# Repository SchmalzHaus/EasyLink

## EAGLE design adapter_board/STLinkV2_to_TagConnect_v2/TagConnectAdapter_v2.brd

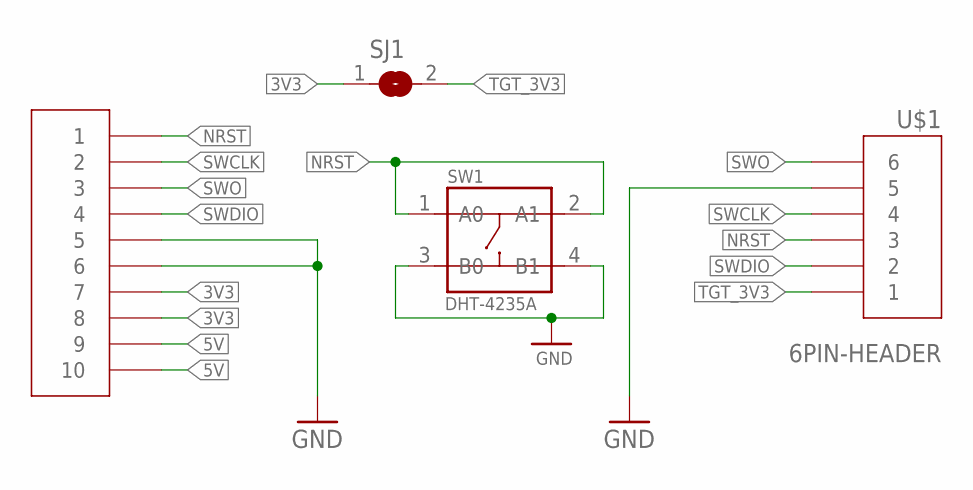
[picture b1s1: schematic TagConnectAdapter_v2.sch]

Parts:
SJ1: SJ
SW1: DHT-4235A; SW4-SMD-4.2X3.2X2.5MM
U$1: 6PIN-HEADER; 2X3_BOARD_EDGE
U$2: SFH11-2X5STRAIGHT; SFH11-2X5-STRAIGHT

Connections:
3V3: SJ1.1, U$2.P7 (7), U$2.P8 (8)
5V: U$2.P9 (9), U$2.P10 (10)
GND: SW1.3 (B0), SW1.4 (B1), U$1.P5 (5), U$2.P5 (5), U$2.P6 (6)
NRST: SW1.1 (A0), SW1.2 (A1), U$1.P3 (3), U$2.P1 (1)
SWCLK: U$1.P4 (4), U$2.P2 (2)
SWDIO: U$1.P2 (2), U$2.P4 (4)
SWO: U$1.P6 (6), U$2.P3 (3)
TGT_3V3: SJ1.2, U$1.P1 (1)

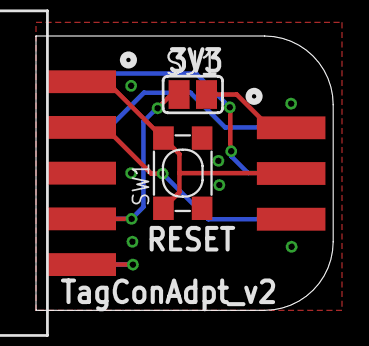
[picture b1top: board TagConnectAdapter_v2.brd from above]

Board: 2 copper layers, 16.5 x 15.2 mm, 4 parts (0 on the bottom side), 8 nets.

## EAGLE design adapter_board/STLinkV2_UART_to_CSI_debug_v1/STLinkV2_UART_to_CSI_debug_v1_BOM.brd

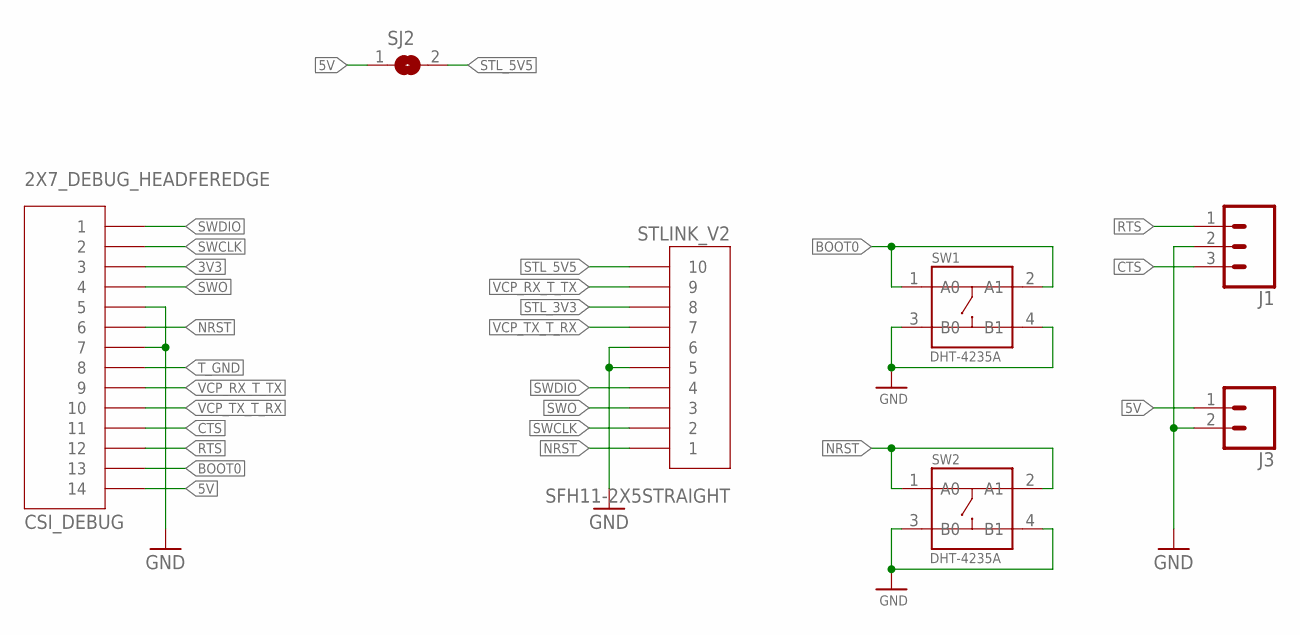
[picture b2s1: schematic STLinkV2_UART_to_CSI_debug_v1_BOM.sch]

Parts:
CSI_DEBUG: 2X7_DEBUG_HEADFEREDGE; 2X7_MALE_BOARD_STRADDLE
J1: CONN_03; 1X03
J3: CONN_02; 1X02
SJ2: SJ
STLINK_V2: SFH11-2X5STRAIGHT; SFH11-2X5-STRAIGHT
SW1, SW2: DHT-4235A; SW4-SMD-4.2X3.2X2.5MM

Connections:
3V3: CSI_DEBUG.P$3 (3)
5V: CSI_DEBUG.P$14 (14), J3.1, SJ2.1
BOOT0: CSI_DEBUG.P$13 (13), SW1.1 (A0), SW1.2 (A1)
CTS: CSI_DEBUG.P$11 (11), J1.3
GND: CSI_DEBUG.P$5 (5), CSI_DEBUG.P$7 (7), J1.2, J3.2, STLINK_V2.P5 (5), STLINK_V2.P6 (6), SW1.3 (B0), SW1.4 (B1), SW2.3 (B0), SW2.4 (B1)
NRST: CSI_DEBUG.P$6 (6), STLINK_V2.P1 (1), SW2.1 (A0), SW2.2 (A1)
RTS: CSI_DEBUG.P$12 (12), J1.1
STL_3V3: STLINK_V2.P8 (8)
STL_5V5: SJ2.2, STLINK_V2.P10 (10)
SWCLK: CSI_DEBUG.P$2 (2), STLINK_V2.P2 (2)
SWDIO: CSI_DEBUG.P$1 (1), STLINK_V2.P4 (4)
SWO: CSI_DEBUG.P$4 (4), STLINK_V2.P3 (3)
T_GND: CSI_DEBUG.P$8 (8)
VCP_RX_T_TX: CSI_DEBUG.P$9 (9), STLINK_V2.P9 (9)
VCP_TX_T_RX: CSI_DEBUG.P$10 (10), STLINK_V2.P7 (7)

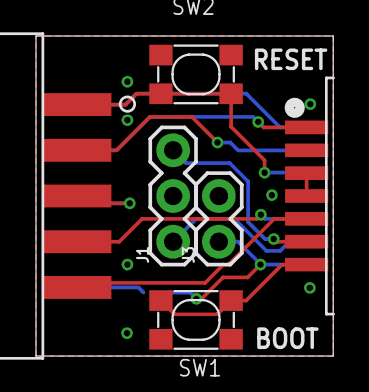
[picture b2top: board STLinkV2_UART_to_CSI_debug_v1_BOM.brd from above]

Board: 2 copper layers, 16.5 x 17.8 mm, 7 parts (1 on the bottom side), 12 nets.

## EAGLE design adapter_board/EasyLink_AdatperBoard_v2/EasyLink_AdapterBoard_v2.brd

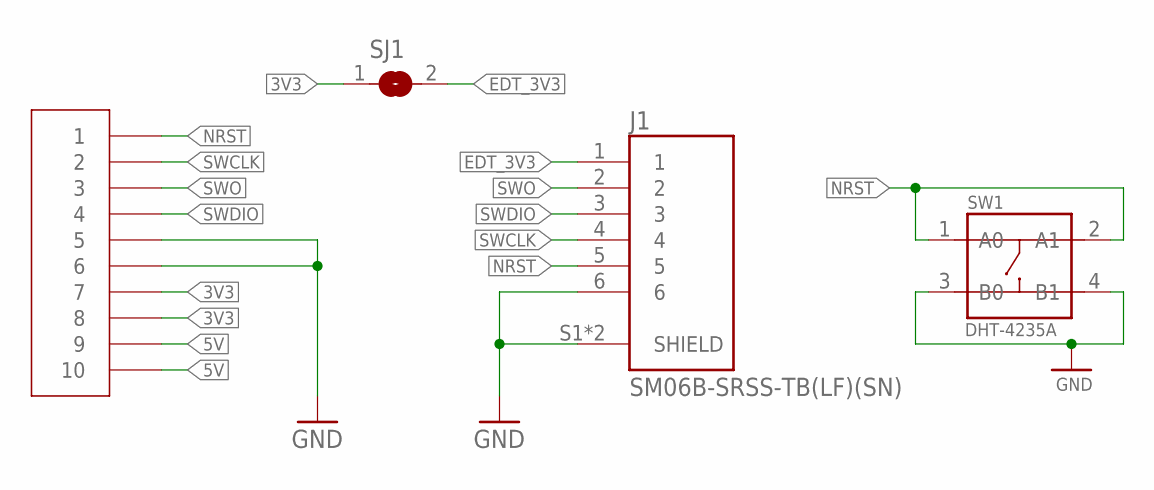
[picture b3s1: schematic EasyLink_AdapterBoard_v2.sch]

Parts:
J1: SM06B-SRSS-TB(LF)(SN); JST_SM06B-SRSS-TB(LF)(SN)
SJ1: SJ
SW1: DHT-4235A; SW4-SMD-4.2X3.2X2.5MM
U$2: SFH11-2X5STRAIGHT; SFH11-2X5-STRAIGHT

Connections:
3V3: SJ1.1, U$2.P7 (7), U$2.P8 (8)
5V: U$2.P9 (9), U$2.P10 (10)
EDT_3V3: J1.1, SJ1.2
GND: J1.6, J1.S1 (SHIELD), J1.S2 (SHIELD), SW1.3 (B0), SW1.4 (B1), U$2.P5 (5), U$2.P6 (6)
NRST: J1.5, SW1.1 (A0), SW1.2 (A1), U$2.P1 (1)
SWCLK: J1.4, U$2.P2 (2)
SWDIO: J1.3, U$2.P4 (4)
SWO: J1.2, U$2.P3 (3)

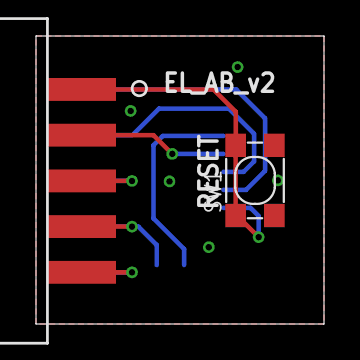
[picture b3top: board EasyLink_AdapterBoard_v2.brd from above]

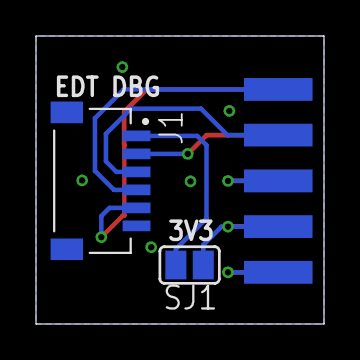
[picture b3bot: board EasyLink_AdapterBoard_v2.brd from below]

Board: 2 copper layers, 16.0 x 16.0 mm, 4 parts (2 on the bottom side), 8 nets.

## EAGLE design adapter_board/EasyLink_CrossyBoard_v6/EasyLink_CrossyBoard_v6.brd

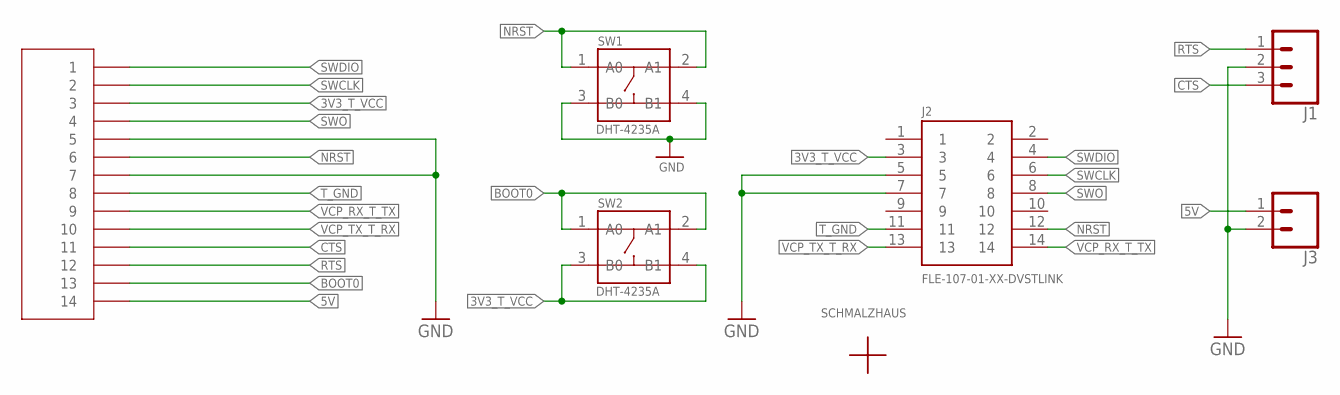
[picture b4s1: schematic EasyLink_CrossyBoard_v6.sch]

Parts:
CN2: 2X7_DEBUG_HEADFEREDGE; 2X7_MALE_BOARD_STRADDLE
J1: CONN_03; 1X03
J2: FLE-107-01-XX-DVSTLINK; ST_LINK_V3_DIRECT
J3: CONN_02; 1X02
SW1, SW2: DHT-4235A; SW4-SMD-4.2X3.2X2.5MM
U$2: SCHMALZHAUSSCHMALZHAUS_SMALL; SCHMALZHAUS_SMALL

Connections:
3V3_T_VCC: CN2.P$3 (3), J2.3, SW2.3 (B0), SW2.4 (B1)
5V: CN2.P$14 (14), J3.1
BOOT0: CN2.P$13 (13), SW2.1 (A0), SW2.2 (A1)
CTS: CN2.P$11 (11), J1.3
GND: CN2.P$5 (5), CN2.P$7 (7), J1.2, J2.5, J2.7, J3.2, SW1.3 (B0), SW1.4 (B1)
NRST: CN2.P$6 (6), J2.12, SW1.1 (A0), SW1.2 (A1)
RTS: CN2.P$12 (12), J1.1
SWCLK: CN2.P$2 (2), J2.6
SWDIO: CN2.P$1 (1), J2.4
SWO: CN2.P$4 (4), J2.8
T_GND: CN2.P$8 (8), J2.11
VCP_RX_T_TX: CN2.P$9 (9), J2.14
VCP_TX_T_RX: CN2.P$10 (10), J2.13

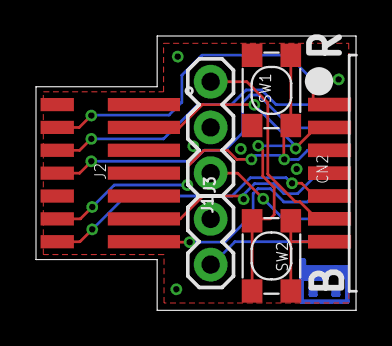
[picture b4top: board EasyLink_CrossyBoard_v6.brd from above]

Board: 2 copper layers, 17.8 x 15.2 mm, 7 parts (1 on the bottom side), 13 nets.

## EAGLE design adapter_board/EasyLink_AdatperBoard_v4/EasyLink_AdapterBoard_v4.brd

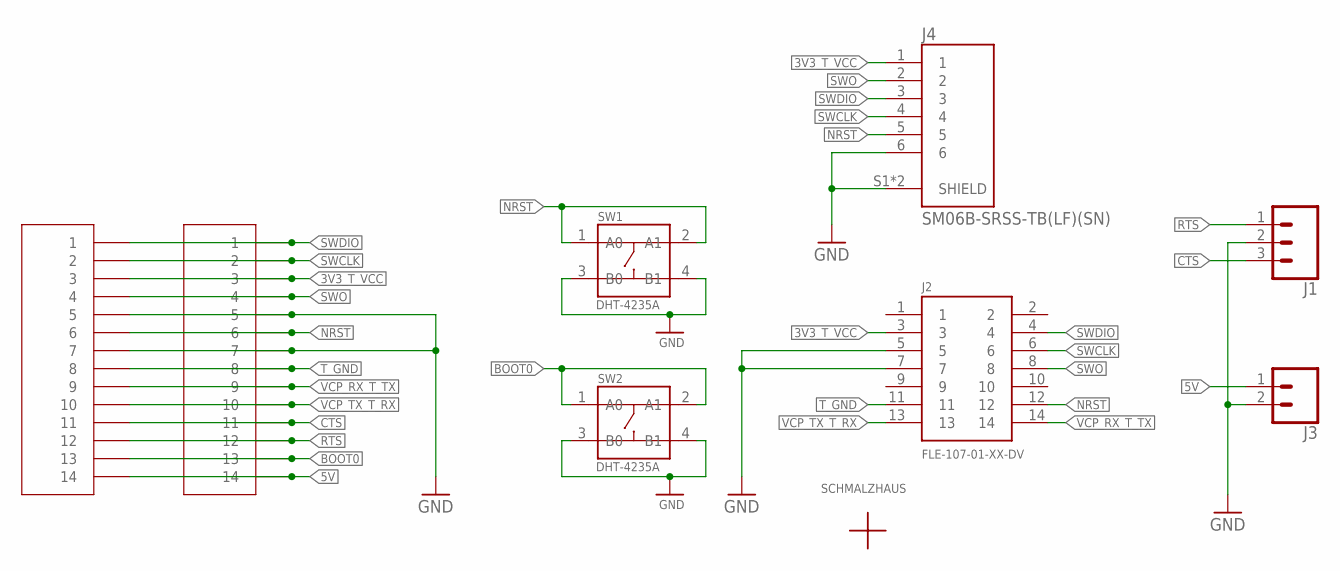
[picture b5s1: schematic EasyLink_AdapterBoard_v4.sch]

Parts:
CN1: 2X7_DEBUG_HEADFER; 20021121_2X7_SMT_MALE
CN2: 2X7_DEBUG_HEADFEREDGE; 2X7_MALE_BOARD_STRADDLE
J1: CONN_03; 1X03
J2: FLE-107-01-XX-DV
J3: CONN_02; 1X02
J4: SM06B-SRSS-TB(LF)(SN); JST_SM06B-SRSS-TB(LF)(SN)
SW1, SW2: DHT-4235A; SW4-SMD-4.2X3.2X2.5MM
U$2: SCHMALZHAUSSCHMALZHAUS_SMALL; SCHMALZHAUS_SMALL

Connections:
3V3_T_VCC: CN1.P$3 (3), CN2.P$3 (3), J2.3, J4.1
5V: CN1.P$14 (14), CN2.P$14 (14), J3.1
BOOT0: CN1.P$13 (13), CN2.P$13 (13), SW2.1 (A0), SW2.2 (A1)
CTS: CN1.P$11 (11), CN2.P$11 (11), J1.3
GND: CN1.P$5 (5), CN1.P$7 (7), CN2.P$5 (5), CN2.P$7 (7), J1.2, J2.5, J2.7, J3.2, J4.6, J4.S1 (SHIELD), J4.S2 (SHIELD), SW1.3 (B0), SW1.4 (B1), SW2.3 (B0), SW2.4 (B1)
NRST: CN1.P$6 (6), CN2.P$6 (6), J2.12, J4.5, SW1.1 (A0), SW1.2 (A1)
RTS: CN1.P$12 (12), CN2.P$12 (12), J1.1
SWCLK: CN1.P$2 (2), CN2.P$2 (2), J2.6, J4.4
SWDIO: CN1.P$1 (1), CN2.P$1 (1), J2.4, J4.3
SWO: CN1.P$4 (4), CN2.P$4 (4), J2.8, J4.2
T_GND: CN1.P$8 (8), CN2.P$8 (8), J2.11
VCP_RX_T_TX: CN1.P$9 (9), CN2.P$9 (9), J2.14
VCP_TX_T_RX: CN1.P$10 (10), CN2.P$10 (10), J2.13

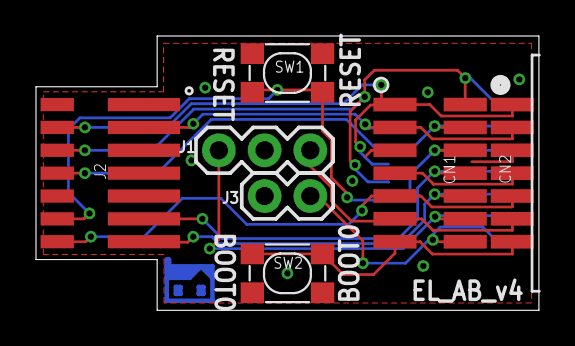
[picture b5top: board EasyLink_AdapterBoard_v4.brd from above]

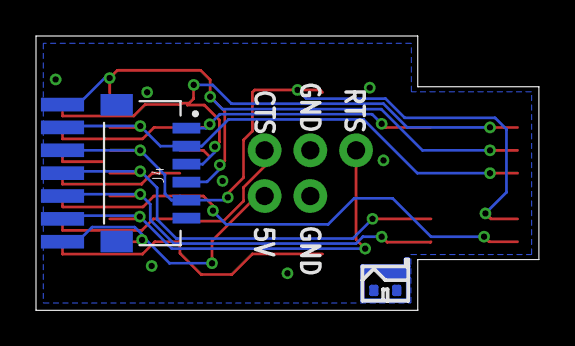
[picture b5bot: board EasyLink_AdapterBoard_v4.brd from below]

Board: 2 copper layers, 27.9 x 15.2 mm, 9 parts (2 on the bottom side), 13 nets.

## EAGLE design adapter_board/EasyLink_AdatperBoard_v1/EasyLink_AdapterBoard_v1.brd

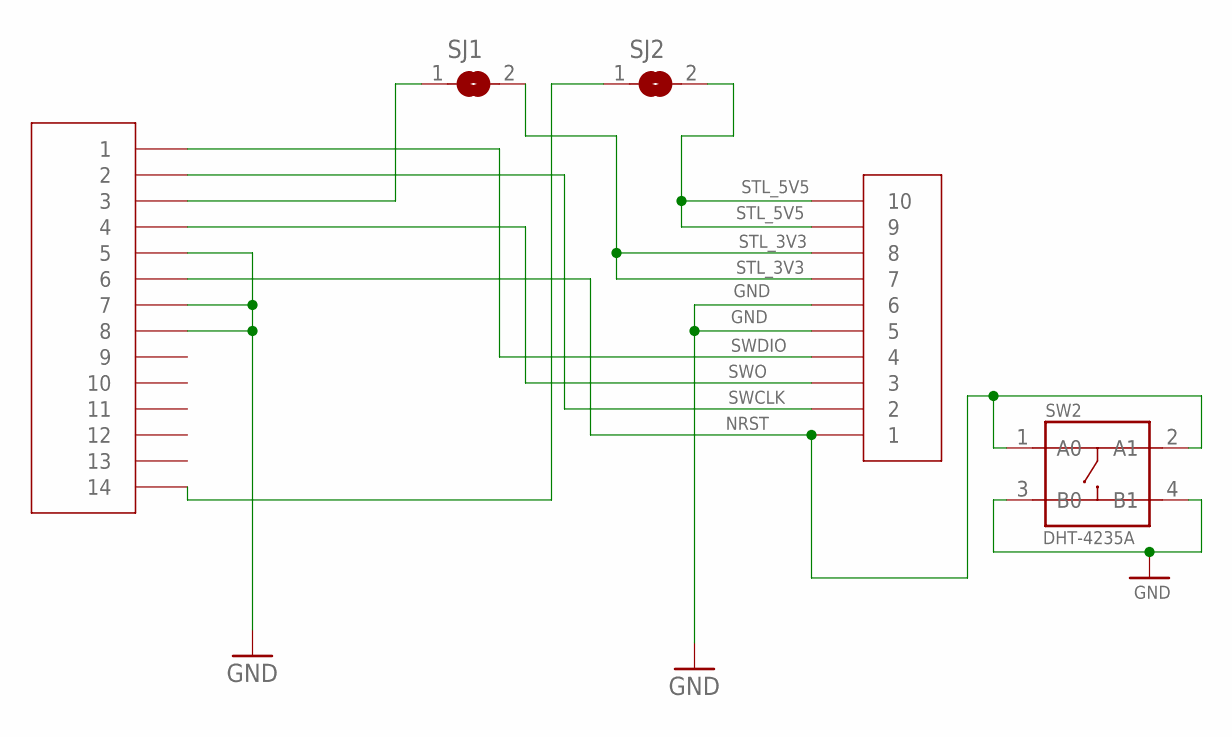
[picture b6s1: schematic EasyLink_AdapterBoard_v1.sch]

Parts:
SJ1, SJ2: SJ
SW2: DHT-4235A; SW4-SMD-4.2X3.2X2.5MM
U$1: 2X7_DEBUG_HEADFER; 20021121_2X7_SMT_MALE
U$2: SFH11-2X5STRAIGHT; SFH11-2X5-STRAIGHT

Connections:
GND: SW2.3 (B0), SW2.4 (B1), U$1.P$5 (5), U$1.P$7 (7), U$1.P$8 (8), U$2.P5 (5), U$2.P6 (6)
unnamed: SJ2.1, U$1.P$14 (14)
unnamed: SJ1.1, U$1.P$3 (3)
NRST: SW2.1 (A0), SW2.2 (A1), U$1.P$6 (6), U$2.P1 (1)
STL_3V3: SJ1.2, U$2.P7 (7), U$2.P8 (8)
STL_5V5: SJ2.2, U$2.P9 (9), U$2.P10 (10)
SWCLK: U$1.P$2 (2), U$2.P2 (2)
SWDIO: U$1.P$1 (1), U$2.P4 (4)
SWO: U$1.P$4 (4), U$2.P3 (3)

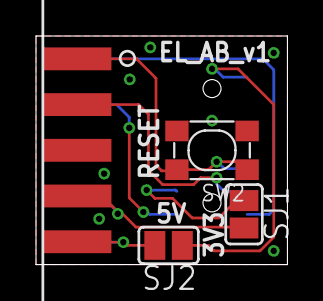
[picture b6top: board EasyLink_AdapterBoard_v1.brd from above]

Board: 4 copper layers, 14.0 x 12.7 mm, 5 parts (1 on the bottom side), 9 nets.

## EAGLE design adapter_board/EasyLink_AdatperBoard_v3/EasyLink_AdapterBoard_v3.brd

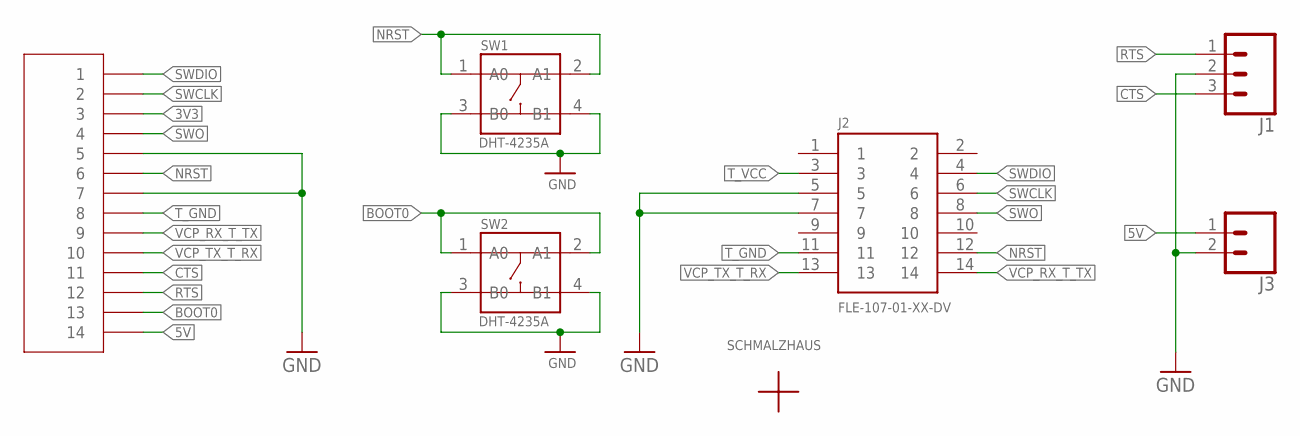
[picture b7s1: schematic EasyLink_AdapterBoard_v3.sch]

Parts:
CN1: 2X7_DEBUG_HEADFEREDGE; 2X7_MALE_BOARD_STRADDLE
J1: CONN_03; 1X03
J2: FLE-107-01-XX-DV
J3: CONN_02; 1X02
SW1, SW2: DHT-4235A; SW4-SMD-4.2X3.2X2.5MM
U$2: SCHMALZHAUSSCHMALZHAUS_SMALL; SCHMALZHAUS_SMALL

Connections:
3V3: CN1.P$3 (3)
5V: CN1.P$14 (14), J3.1
BOOT0: CN1.P$13 (13), SW2.1 (A0), SW2.2 (A1)
CTS: CN1.P$11 (11), J1.3
GND: CN1.P$5 (5), CN1.P$7 (7), J1.2, J2.5, J2.7, J3.2, SW1.3 (B0), SW1.4 (B1), SW2.3 (B0), SW2.4 (B1)
NRST: CN1.P$6 (6), J2.12, SW1.1 (A0), SW1.2 (A1)
RTS: CN1.P$12 (12), J1.1
SWCLK: CN1.P$2 (2), J2.6
SWDIO: CN1.P$1 (1), J2.4
SWO: CN1.P$4 (4), J2.8
T_GND: CN1.P$8 (8), J2.11
T_VCC: J2.3
VCP_RX_T_TX: CN1.P$9 (9), J2.14
VCP_TX_T_RX: CN1.P$10 (10), J2.13

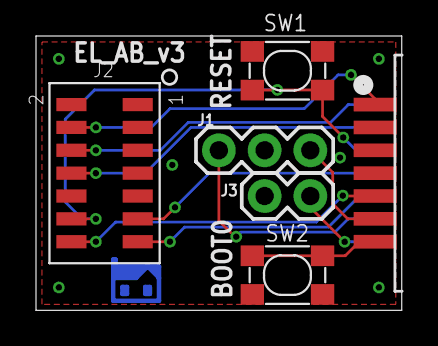
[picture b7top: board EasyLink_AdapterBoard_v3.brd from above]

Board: 2 copper layers, 20.3 x 15.2 mm, 7 parts (1 on the bottom side), 12 nets.

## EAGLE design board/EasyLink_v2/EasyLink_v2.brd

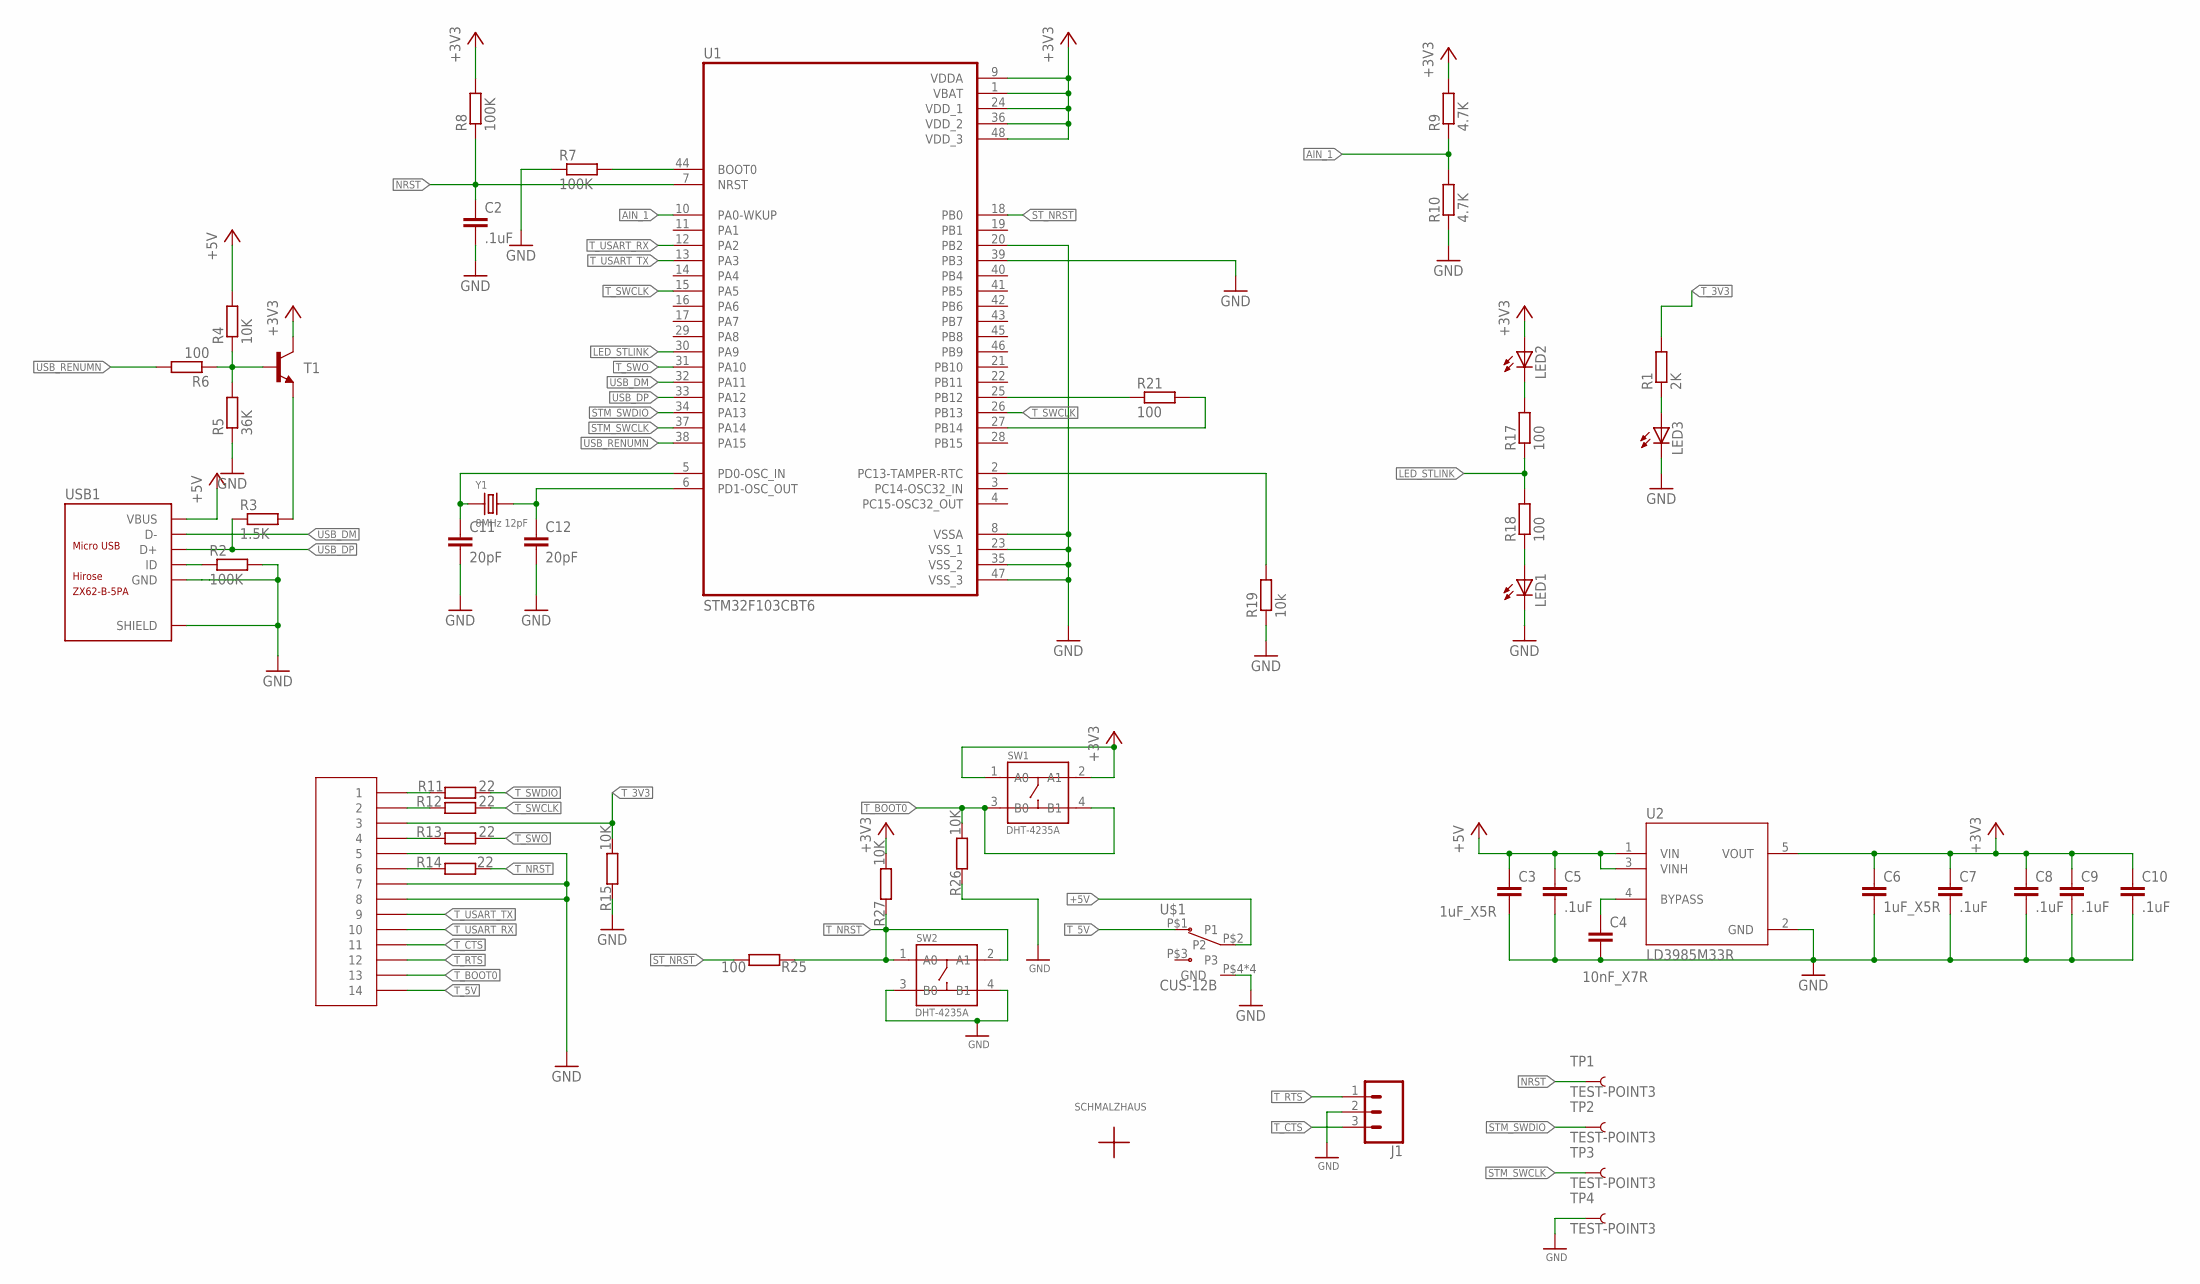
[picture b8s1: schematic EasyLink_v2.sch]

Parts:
C2, C5, C7, C8, C9, C10: .1uF; C0603
C3, C6: 1uF_X5R; C0603
C4: 10nF_X7R; C0603
C11, C12: 20pF; C0603
CN1: 2X7_DEBUG_HEADFEREDGE; 2X7_MALE_BOARD_STRADDLE
J1: CONN_031X03_NO_SILK; 1X03_NO_SILK
LED1, LED2, LED3: LED_ESML0603; LED_SML0603
R1: 2K; R0603
R2, R7, R8: 100K; R0603
R3: 1.5K; R0603
R4, R15, R26, R27: 10K; R0603
R5: 36K; R0603
R6, R17, R18, R21, R25: 100; R0603
R9, R10: 4.7K; R0603
R11, R12, R13, R14: 22; R0603
R19: 10k; R0603
SW1, SW2: DHT-4235A; SW4-SMD-4.2X3.2X2.5MM
T1: BCF30-NPN-SOT23-BEC; SOT23-BEC
TP1, TP2, TP3, TP4: TEST-POINT3; PAD.03X.03
U1: STM32F103CBT6; QFP50P900X900X160-48N
U2: LD3985M33R; SOT95P280X145-5N
U$1: CUS-12B
U$2: SCHMALZHAUSSCHMALZHAUS_SMALL; SCHMALZHAUS_SMALL
USB1: ZX62-B-5PA; MICRO-USB5+6P-SMD-0.65-AB
Y1: 8MHz 12pF; X2-SMD-5.0X3.2X1.3MM

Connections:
+3V3: C6.1, C7.1, C8.1, C9.1, C10.1, LED2.A, R8.2, R9.2, R27.2, SW1.1 (A0), SW1.2 (A1), T1.C, U1.1 (VBAT), U1.9 (VDDA), U1.24 (VDD_1), U1.36 (VDD_2), U1.48 (VDD_3), U2.5 (VOUT)
+5V: C3.1, C5.1, R4.2, U2.1 (VIN), U2.3 (VINH), U$1.P$2 (P2), USB1.1 (VBUS)
AIN_1: R9.1, R10.2, U1.10 (PA0-WKUP)
GND: C2.2, C3.2, C4.2, C5.2, C6.2, C7.2, C8.2, C9.2, C10.2, C11.2, C12.2, CN1.P$5 (5), CN1.P$7 (7), CN1.P$8 (8), J1.2, LED1.C, LED3.C, R2.2, R5.1, R7.1, R10.1, R15.1, R19.1, R26.1, SW2.3 (B0), SW2.4 (B1), TP4.P$1, U1.8 (VSSA), U1.20 (PB2), U1.23 (VSS_1), U1.35 (VSS_2), U1.39 (PB3), U1.47 (VSS_3), U2.2 (GND), U$1.P$4 (GND), U$1.P$5 (GND), U$1.P$6 (GND), U$1.P$7 (GND), USB1.5 (GND), USB1.P1 (SHIELD), USB1.P2 (SHIELD), USB1.P3 (SHIELD), USB1.P4 (SHIELD), USB1.P5 (SHIELD), USB1.P6 (SHIELD)
LED_STLINK: R17.1, R18.2, U1.30 (PA9)
unnamed: R3.2, T1.E
unnamed: CN1.P$1 (1), R11.1
unnamed: CN1.P$2 (2), R12.1
unnamed: CN1.P$4 (4), R13.1
unnamed: CN1.P$6 (6), R14.1
unnamed: R7.2, U1.44 (BOOT0)
unnamed: R2.1, USB1.4 (ID)
unnamed: LED1.A, R18.1
unnamed: R4.1, R5.2, R6.1, T1.B
unnamed: LED2.C, R17.2
unnamed: R21.2, U1.27 (PB14)
unnamed: C4.1, U2.4 (BYPASS)
unnamed: LED3.A, R1.1
unnamed: R19.2, U1.2 (PC13-TAMPER-RTC)
unnamed: C11.1, U1.5 (PD0-OSC_IN), Y1.1
unnamed: C12.1, U1.6 (PD1-OSC_OUT), Y1.2
NRST: C2.1, R8.1, TP1.P$1, U1.7 (NRST)
STM_SWCLK: TP3.P$1, U1.37 (PA14)
STM_SWDIO: TP2.P$1, U1.34 (PA13)
ST_NRST: R25.2, U1.18 (PB0)
T_3V3: CN1.P$3 (3), R1.2, R15.2
T_5V: CN1.P$14 (14), U$1.P$1 (P1)
T_BOOT0: CN1.P$13 (13), R26.2, SW1.3 (B0), SW1.4 (B1)
T_CTS: CN1.P$11 (11), J1.3
T_NRST: R14.2, R25.1, R27.1, SW2.1 (A0), SW2.2 (A1)
T_RTS: CN1.P$12 (12), J1.1
T_SWCLK: R12.2, U1.15 (PA5), U1.26 (PB13)
T_SWDIO: R11.2, R21.1, U1.25 (PB12)
T_SWO: R13.2, U1.31 (PA10)
T_USART_RX: CN1.P$10 (10), U1.12 (PA2)
T_USART_TX: CN1.P$9 (9), U1.13 (PA3)
USB_DM: U1.32 (PA11), USB1.2 (D-)
USB_DP: R3.1, U1.33 (PA12), USB1.3 (D+)
USB_RENUMN: R6.2, U1.38 (PA15)

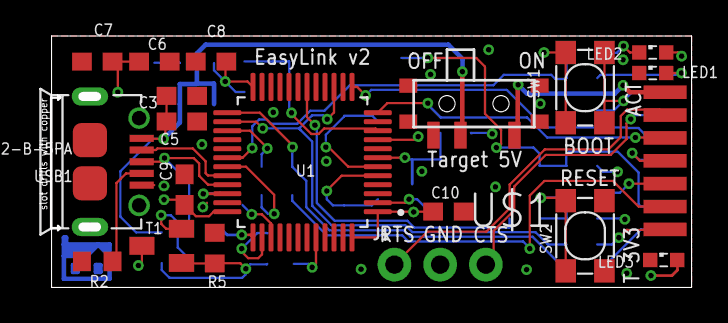
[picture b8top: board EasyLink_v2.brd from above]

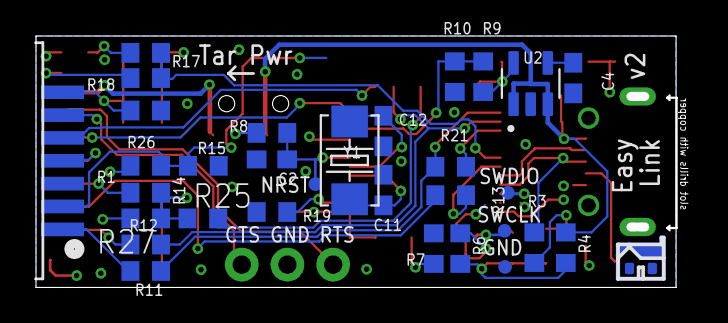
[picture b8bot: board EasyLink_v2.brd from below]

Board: 4 copper layers, 35.6 x 14.0 mm, 51 parts (32 on the bottom side), 39 nets.

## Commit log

2019-06-17 Starting the project up.
2019-06-17 A bit more work on the BOM.
2019-06-18 Added png of orig schematic
2019-06-19 Starting new adapter board
2019-06-19 Added some parts
2019-06-20 EasyLink adapter board v1 done and sent to JLC
2019-06-25 Updating BOMs, starting new board.
2019-06-26 More work on adapter board - got CPU in.
2019-06-28 Starting notest.txt file
2019-06-29 v1 of EasyLink sent to JLC for fab
2019-06-30 Adapter Board v2 done : set up for Larry and the EDT display
2019-07-01 Updated BOM and ordered parts
2019-07-02 Remade gerbers because I forgot to add in the board outline and JLC rejected it.
2019-07-09 Fixed names and values layers for population.
2019-07-10 Added low profile switch option
2019-07-11 Added new 14 pin header footprint
2019-07-11 Start of v2 EasyLink
2019-07-11 WIP: V2 EasyLink
2019-07-11 More WIP
2019-07-23 Starting the reverse engineering of the ST-Link V2
2019-07-26 Adapter board v3, which adapts from the ST-Link-V3MINI to CSI 14 pin programming cable.
2019-07-27 Adapter board v4 started (with T_VCC connected and standard surface mount CSI connector.
2019-08-01 Added net names.
2019-08-05 After testing out V3 with ST_Link_v3s, some mods to help make the board better. Added edge connector and EDT connector.
2019-08-05 New STLinkV3 connector design to make soldering directly to STLink board easier.
2019-08-06 Finished the v4 design, sent off to JLCPCB. Also screwed up the schematic by editing the panel board file with a separate name. Looks like we're missinga checkin of the debug header library?
2019-08-23 Now called "Crossy Board V5", much smaller than v4 adapter board, sent off to JLC.
2019-09-01 Crossy Board V6 sent to fab. Got blue this time, slow boat from China. Fixed BOOT0 bug.
2019-09-17 Updated v2 adapter board (EDT debug connector from ST-Link-V2 clone) to be 15mm x 15mm so that JLC can panelize them without extra charge.
2019-09-19 Moved copper away from edges for v-score, bumped size to 16mm x 16mm so JLC doesn't charge extra for vscoring.
2020-01-14 Created TagConnect adapter board.
2020-02-02 Added the STLinkV2 UART to CSI Debug board. WIP.
2020-02-03 Final board design tweaked, sent to JLC
2020-02-03 BOM update
2020-02-09 Added STLinkV2_to_TagConnect_v2

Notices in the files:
parts and their libraries:
SparkFun-Connectors: Licensing: Creative Commons ShareAlike 4.0 International - https://creativecommons.org/licenses/by-sa/4.0
